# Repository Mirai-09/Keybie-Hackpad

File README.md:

# Keybie - Hackpad  

Keybie is a 12-key macropad with a rotary encoder and an OLED display! It uses KMK firmware and is my first-ever hardware project with a PCB. :)<br>
You can customise Keybie to any Keyboard shortcuts and have the shortcut at your hand!<br><br>
Firmware of Keybie comes with following functions:
 - media control (prev track, pause track, next track)
 - Volume control (volume up and down with scroll knob, mute with a key)
 - Up, Down, Right and Left keys
 - Brightness Control (increase, decrease)
 - F11 (full screen on chrome)
 - Screenshot  

I made Keybie for Blueprint, a YSWS of Hack Club! I wanted to make this because macropads seems cool and I wanted to try building a hardware project myself! :)  

# BOM  

My macropad includes materials that are given by Hack Club!    
12x Through-hole 1N4148 Diodes  
12x MX-Style switches  
1x EC11 Rotary encoders  
1x 0.91 inch OLED displays  
12x Blank DSA keycaps  

# PCB  
Here is my PCB! Made in KiCad (took me forever to decide what to include ngl T-T)
  
3D!  
  
Schematic:  

# CAD  
Here is my case! Made in Fusion 360 (Also took me forever to design it T-T)  
Bottom:  

Top:  

All components together:

# Assembled Keybie
This is how my Keybie looks in real life! (Also took me forever yes T-T)

Learned a lot while working on this :)

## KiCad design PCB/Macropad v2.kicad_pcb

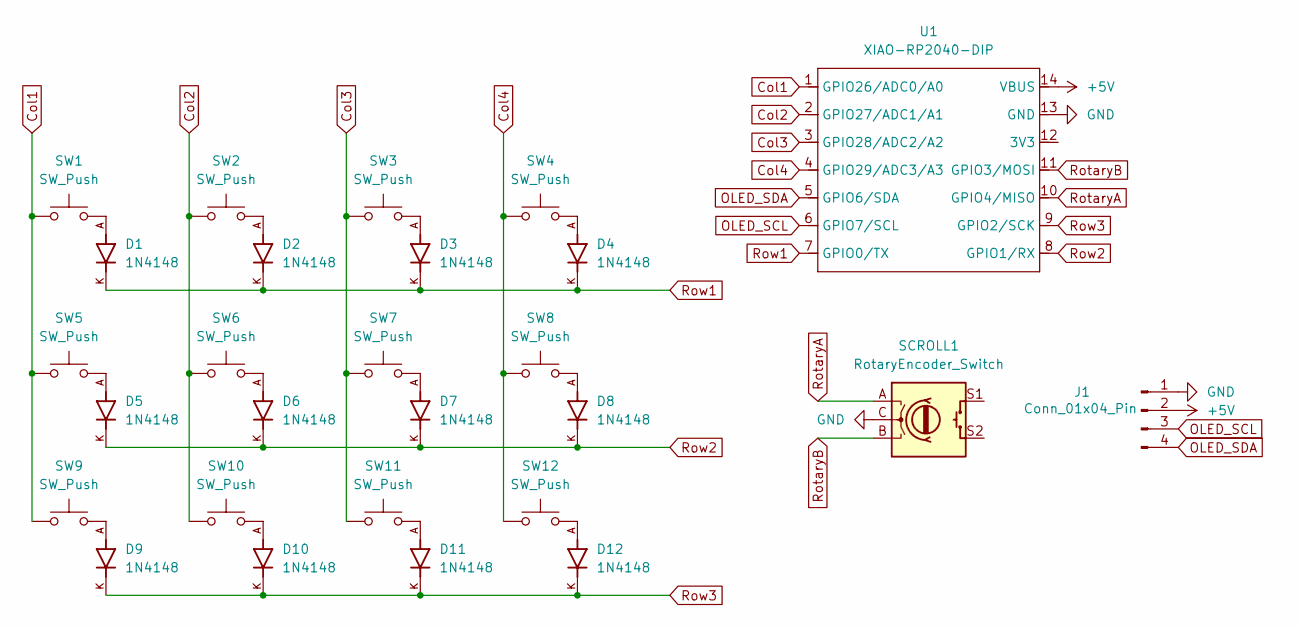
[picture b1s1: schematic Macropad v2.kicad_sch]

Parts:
D1, D2, D3, D4, D5, D6, D7, D8, D9, D10, D11, D12: 1N4148; DIOAD753W49L380D172B; PARTREV 5
J1: Conn_01x04_Pin; SSD1306-0.91-OLED-4pin-128x32
SCROLL1: RotaryEncoder_Switch; RotaryEncoder_Alps_EC11E-Switch_Vertical_H20mm
SW1, SW2, SW3, SW4, SW5, SW6, SW7, SW8, SW9, SW10, SW11, SW12: SW_Push; SW_Cherry_MX_1.00u_PCB
U1: XIAO-RP2040-DIP

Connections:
+5V: J1.2, U1.14 (VBUS)
Col1: SW1.1, SW5.1, SW9.1, U1.1 (GPIO26/ADC0/A0)
Col2: SW2.1, SW6.1, SW10.1, U1.2 (GPIO27/ADC1/A1)
Col3: SW3.1, SW7.1, SW11.1, U1.3 (GPIO28/ADC2/A2)
Col4: SW4.1, SW8.1, SW12.1, U1.4 (GPIO29/ADC3/A3)
GND: J1.1, SCROLL1.C, U1.13 (GND)
unnamed: D1.A, SW1.2
unnamed: D2.A, SW2.2
unnamed: D3.A, SW3.2
unnamed: D4.A, SW4.2
unnamed: D5.A, SW5.2
unnamed: D6.A, SW6.2
unnamed: D7.A, SW7.2
unnamed: D8.A, SW8.2
unnamed: D9.A, SW9.2
unnamed: D10.A, SW10.2
unnamed: D11.A, SW11.2
unnamed: D12.A, SW12.2
OLED_SCL: J1.3, U1.6 (GPIO7/SCL)
OLED_SDA: J1.4, U1.5 (GPIO6/SDA)
RotaryA: SCROLL1.A, U1.10 (GPIO4/MISO)
RotaryB: SCROLL1.B, U1.11 (GPIO3/MOSI)
Row1: D1.K, D2.K, D3.K, D4.K, U1.7 (GPIO0/TX)
Row2: D5.K, D6.K, D7.K, D8.K, U1.8 (GPIO1/RX)
Row3: D9.K, D10.K, D11.K, D12.K, U1.9 (GPIO2/SCK)

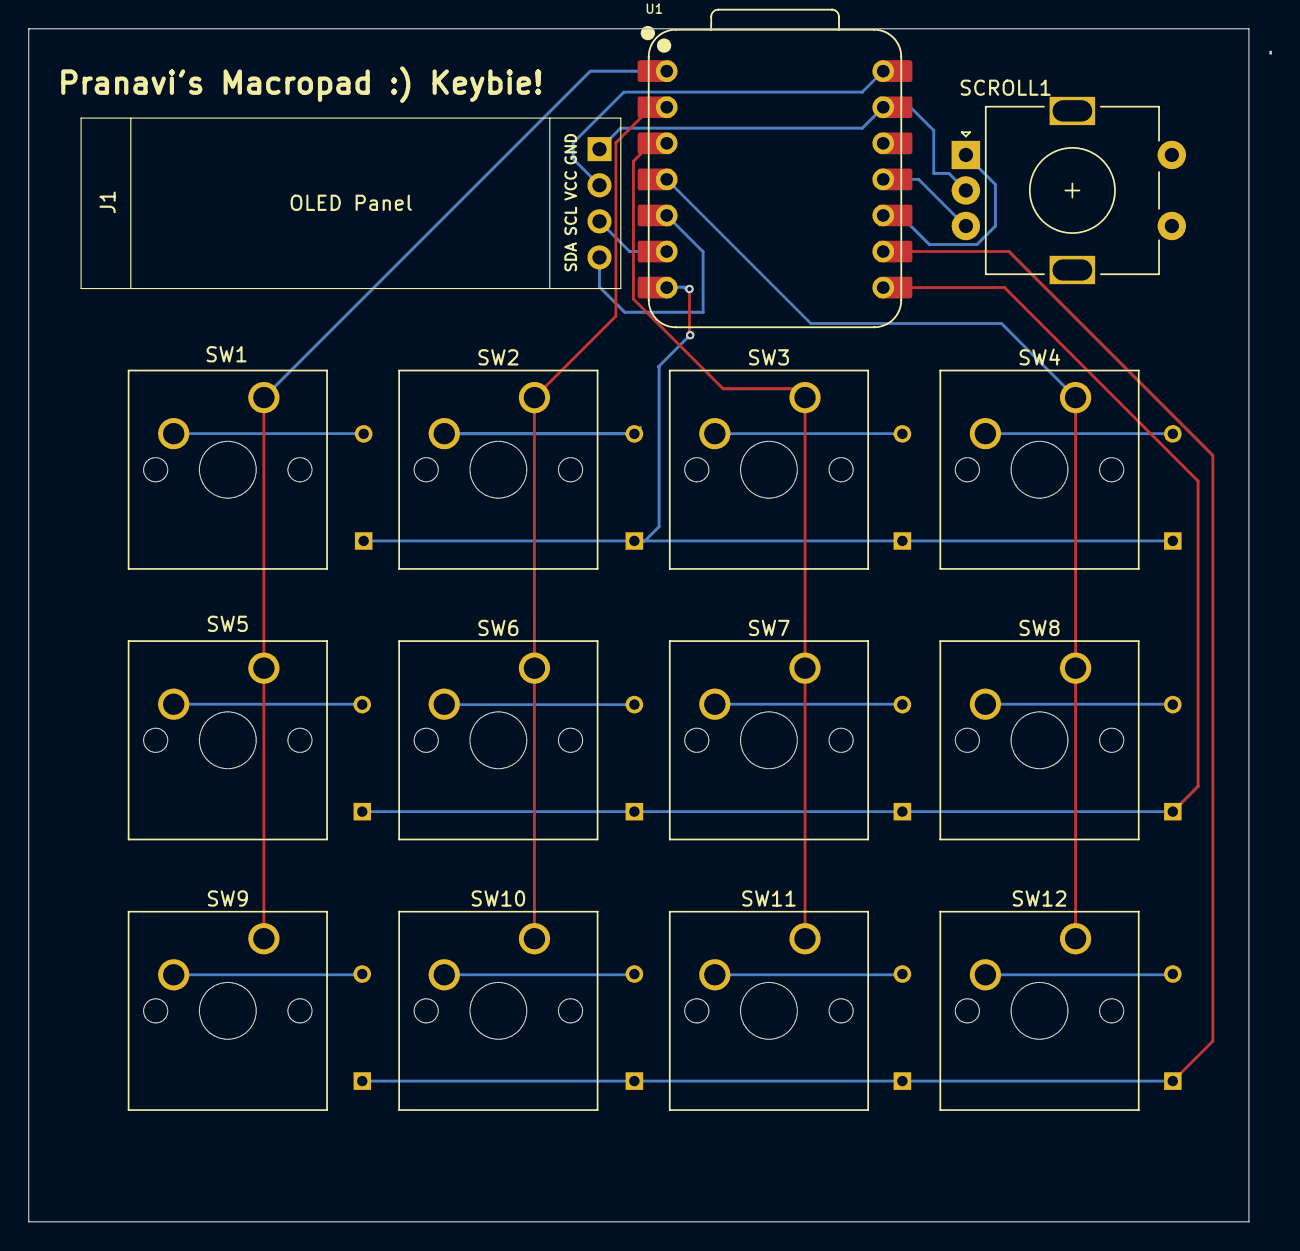
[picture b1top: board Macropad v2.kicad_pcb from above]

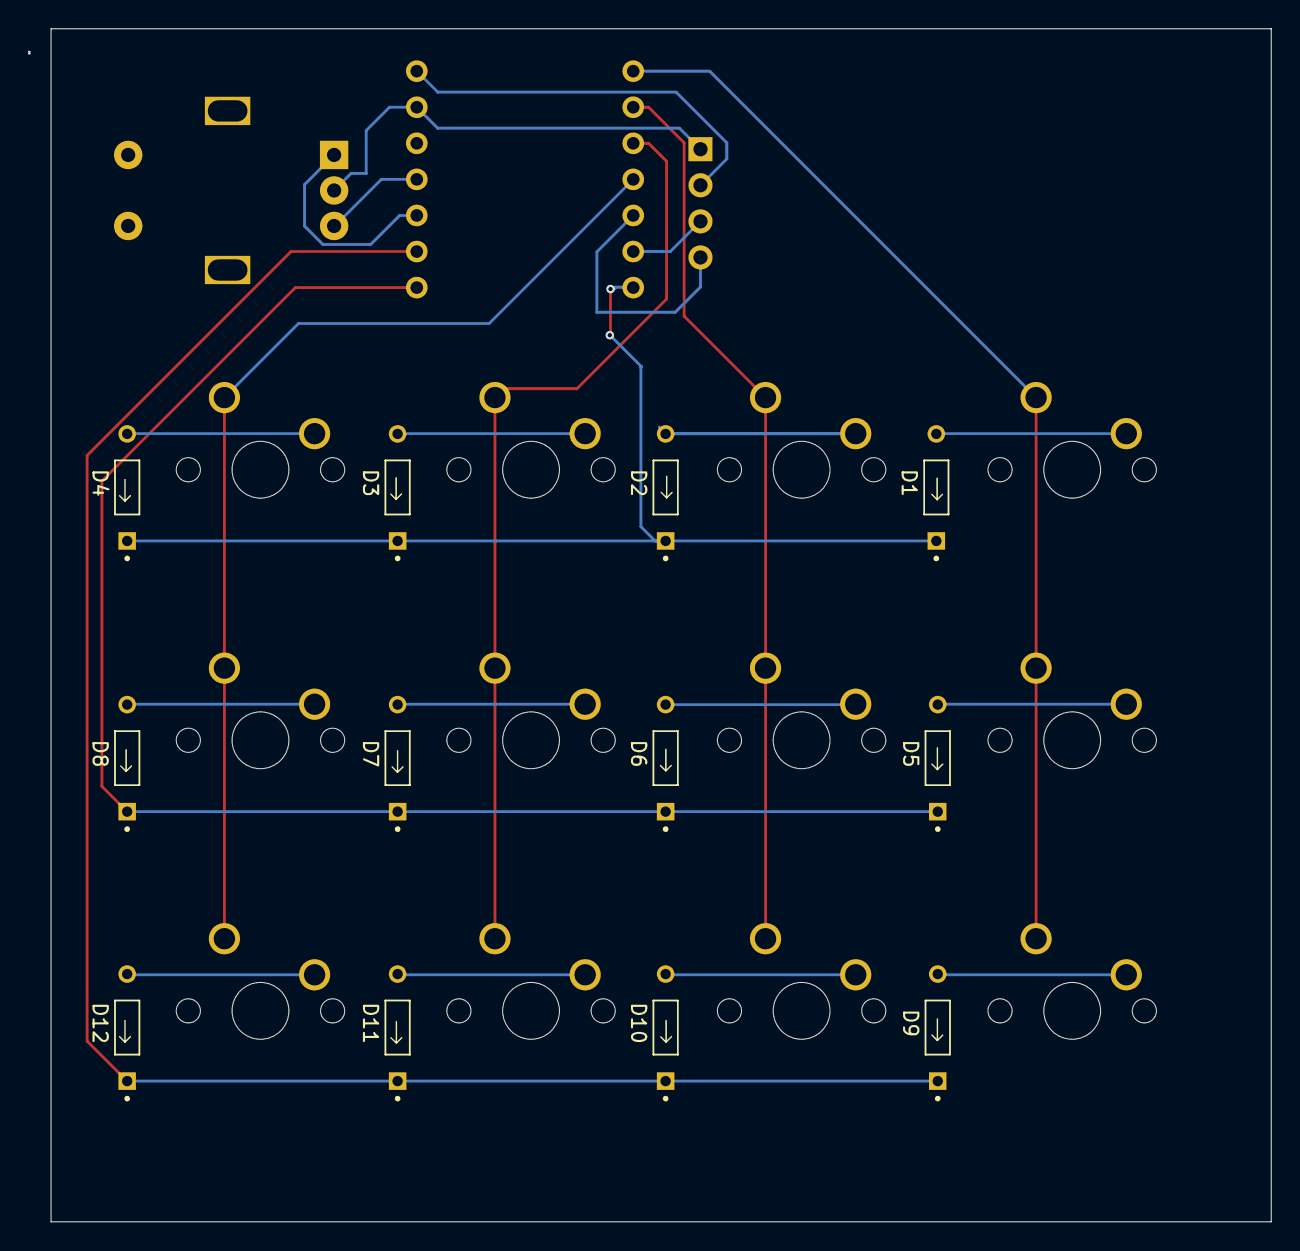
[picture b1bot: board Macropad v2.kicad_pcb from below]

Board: 2 copper layers, 87.5 x 84.0 mm, 27 parts (12 on the bottom side), 25 nets.

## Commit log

2026-01-16 Adding CAD Files of Keybie
2026-01-16 PCB Files
2026-01-16 Firmware using kmk!
2026-01-16 Update README.md
    I keep forgetting there is a preview option T-T
2026-01-17 Changes
    Changes I did after review
2026-01-17 Update README.md
    Made some changes to PCB and assembly. So updated the screenshot
2026-03-03 Final files of Keybie
    Updated CASE, PCB and firmware
2026-03-03 Update README.md
    Updated CAD pics and added real life model pic
2026-03-04 Added more CAD files
2026-03-14 Update README.md
    Spelling Updates
